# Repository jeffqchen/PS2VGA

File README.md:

# PS2VGA

This is an RGB+CSync video and stereo audio analogue output dongle, with a VGA port, a 3.5mm jack and an RCA jack, for the entire PlayStation family. It is a member from my [Console VGA Dongle Series](https://github.com/jeffqchen/Console-VGA-Dongle-Series).

Please refer to the **[Project Wiki](https://github.com/jeffqchen/PS2VGA/wiki)** regarding technical details, parts and building guide.

---------
## Special Thanks

- Mike Chi of [RetroTINK](https://www.retrotink.com) - [Twitter](https://twitter.com/retrotink2)

- Javier Rodas - [Twitter](https://twitter.com/JaviRodasG)

- Retro Gamer Stuff (Bad_Ad84) - [Twitter](https://twitter.com/RetroGamerStuff)

--------
Shield: [![CC BY-SA 4.0][cc-by-sa-shield]][cc-by-sa]

This work is licensed under a
[Creative Commons Attribution-ShareAlike 4.0 International License][cc-by-sa].

[![CC BY-SA 4.0][cc-by-sa-image]][cc-by-sa]

[cc-by-sa]: http://creativecommons.org/licenses/by-sa/4.0/
[cc-by-sa-image]: https://licensebuttons.net/l/by-sa/4.0/88x31.png
[cc-by-sa-shield]: https://img.shields.io/badge/License-CC%20BY--SA%204.0-lightgrey.svg

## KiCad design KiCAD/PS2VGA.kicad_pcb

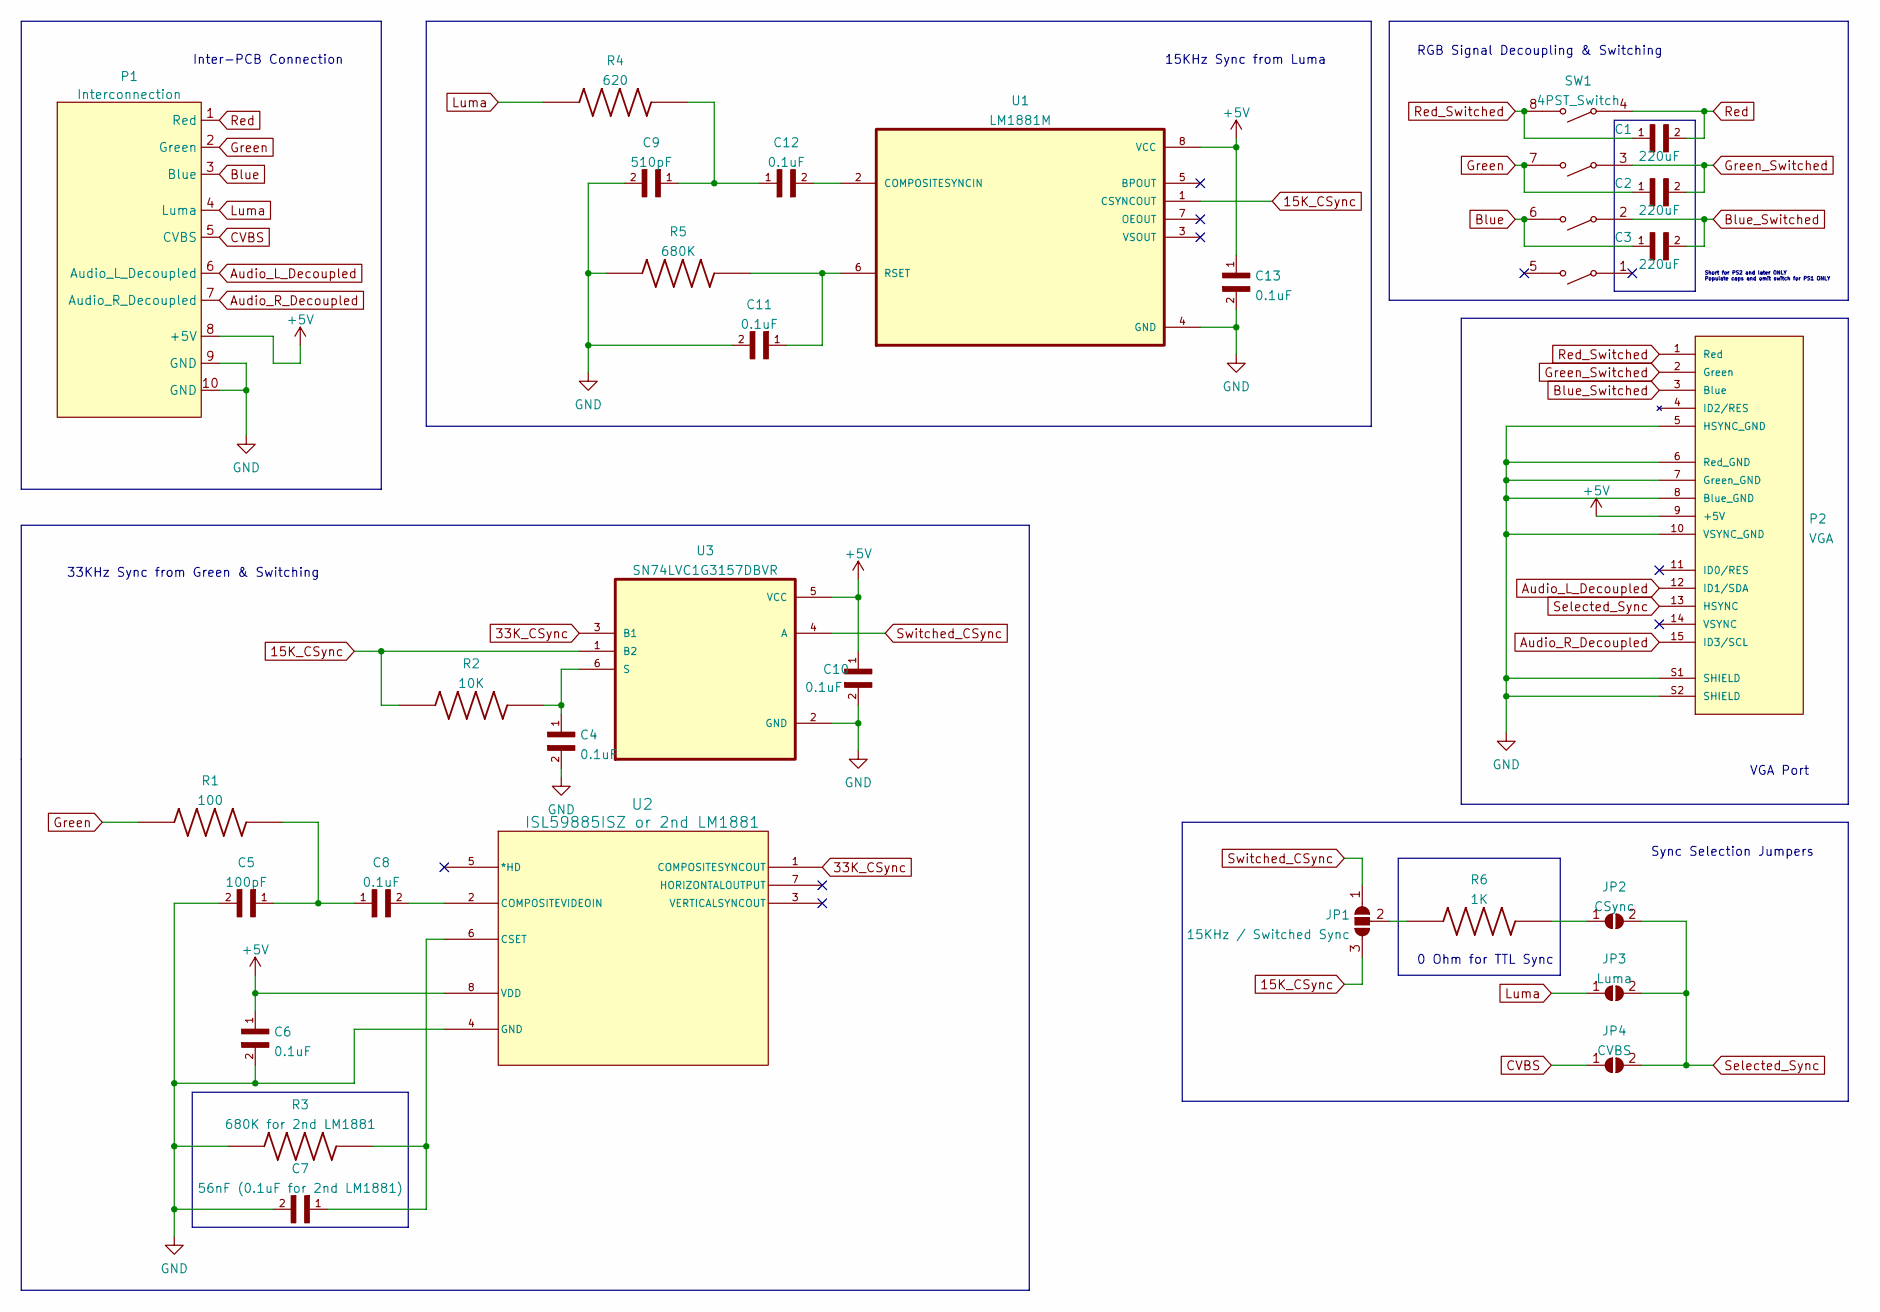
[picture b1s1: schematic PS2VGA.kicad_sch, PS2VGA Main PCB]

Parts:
C1, C2, C3: 220uF; C_1206_3216Metric
C4, C6, C8, C10, C11, C12, C13: 0.1uF; C_0603_1608Metric
C5: 100pF; C_0603_1608Metric
C7: 56nF (0.1uF for 2nd LM1881); C_0603_1608Metric
C9: 510pF; C_0603_1608Metric
JP1: 15KHz / Switched Sync; SolderJumper-3_P1.3mm_Open_RoundedPad1.0x1.5mm
JP2: CSync; SolderJumper-2_P1.3mm_Open_RoundedPad1.0x1.5mm
JP3: Luma; SolderJumper-2_P1.3mm_Open_RoundedPad1.0x1.5mm
JP4: CVBS; SolderJumper-2_P1.3mm_Open_RoundedPad1.0x1.5mm
P1: Interconnection
P2: VGA; VGA_female_rightangle_slim
R1: 100; R_0603_1608Metric
R2: 10K; R_0603_1608Metric
R3: 680K for 2nd LM1881; R_0603_1608Metric
R4: 620; R_0603_1608Metric
R5: 680K; R_0603_1608Metric
R6: 1K; R_0603_1608Metric
SW1: 4PST_Switch; 4PST Switch
U1: LM1881M; LM1881
U2: ISL59885ISZ or 2nd LM1881; ISL59885ISZ-ND
U3: SN74LVC1G3157DBVR

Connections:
15K_CSync: JP1.3 (B), R2.1, U1.1 (CSYNCOUT), U3.1 (B2); also elsewhere on the board
33K_CSync: U2.1 (COMPOSITESYNCOUT), U3.3 (B1)
+5V: C6.1, C10.1, C13.1, P1.8 (+5V), P2.9 (+5V), U1.8 (VCC), U2.8 (VDD), U3.5 (VCC); also elsewhere on the board
Audio_L_Decoupled: P1.6 (Audio_L_Decoupled), P2.12 (ID1/SDA)
Audio_R_Decoupled: P1.7 (Audio_R_Decoupled), P2.15 (ID3/SCL)
Blue: C3.1, P1.3 (Blue), SW1.6
Blue_Switched: C3.2, P2.3 (Blue), SW1.2
CVBS: JP4.1 (A), P1.5 (CVBS)
GND: C4.2, C5.2, C6.2, C7.2, C9.2, C10.2, C11.2, C13.2, P1.9 (GND), P1.10 (GND), P2.5 (HSYNC_GND), P2.6 (Red_GND), P2.7 (Green_GND), P2.8 (Blue_GND), P2.10 (VSYNC_GND), P2.S1 (SHIELD), P2.S2 (SHIELD), R3.1, R5.1, U1.4 (GND), U2.4 (GND), U3.2 (GND); also elsewhere on the board
Green: C2.1, P1.2 (Green), R1.1, SW1.7
Green_Switched: C2.2, P2.2 (Green), SW1.3
Luma: JP3.1 (A), P1.4 (Luma), R4.1
unnamed: C4.1, R2.2, U3.6 (S)
unnamed: C5.1, C8.1, R1.2
unnamed: C7.1, R3.2, U2.6 (CSET)
unnamed: C8.2, U2.2 (COMPOSITEVIDEOIN)
unnamed 16: C11.1, R5.2, U1.6 (RSET); also elsewhere on the board
unnamed: C9.1, C12.1, R4.2
unnamed 18: C12.2, U1.2 (COMPOSITESYNCIN); also elsewhere on the board
unnamed: JP1.2 (C), R6.1
unnamed: JP2.1 (A), R6.2
Red: C1.2, P1.1 (Red), SW1.4
Red_Switched: C1.1, P2.1 (Red), SW1.8
Selected_Sync: JP2.2 (B), JP3.2 (B), JP4.2 (B), P2.13 (HSYNC)
Switched_CSync: JP1.1 (A), U3.4 (A)

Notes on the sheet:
RGB Signal Decoupling & Switching
33KHz Sync from Green & Switching
0 Ohm for TTL Sync
Inter-PCB Connection
VGA Port
Short for PS2 and later ONLY Populate caps and omit switch for PS1 ONLY
15KHz Sync from Luma
Sync Selection Jumpers

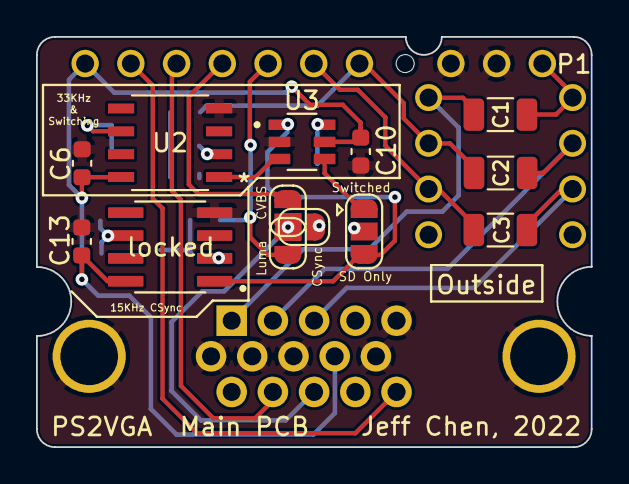
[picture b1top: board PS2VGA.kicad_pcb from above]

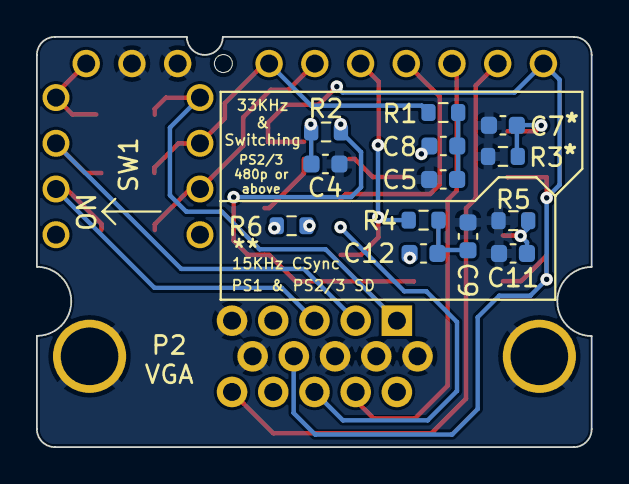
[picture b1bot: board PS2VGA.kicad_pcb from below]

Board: 2 copper layers, 30.8 x 22.8 mm, 29 parts (15 on the bottom side), 25 nets.

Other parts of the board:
locked: LM1881M; LM1881

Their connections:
15K_CSync: locked.1 (CSYNCOUT); also elsewhere on the board
+5V: locked.8 (VCC); also elsewhere on the board
GND: locked.4 (GND); also elsewhere on the board
unnamed 16: locked.6 (RSET); also elsewhere on the board
unnamed 18: locked.2 (COMPOSITESYNCIN); also elsewhere on the board

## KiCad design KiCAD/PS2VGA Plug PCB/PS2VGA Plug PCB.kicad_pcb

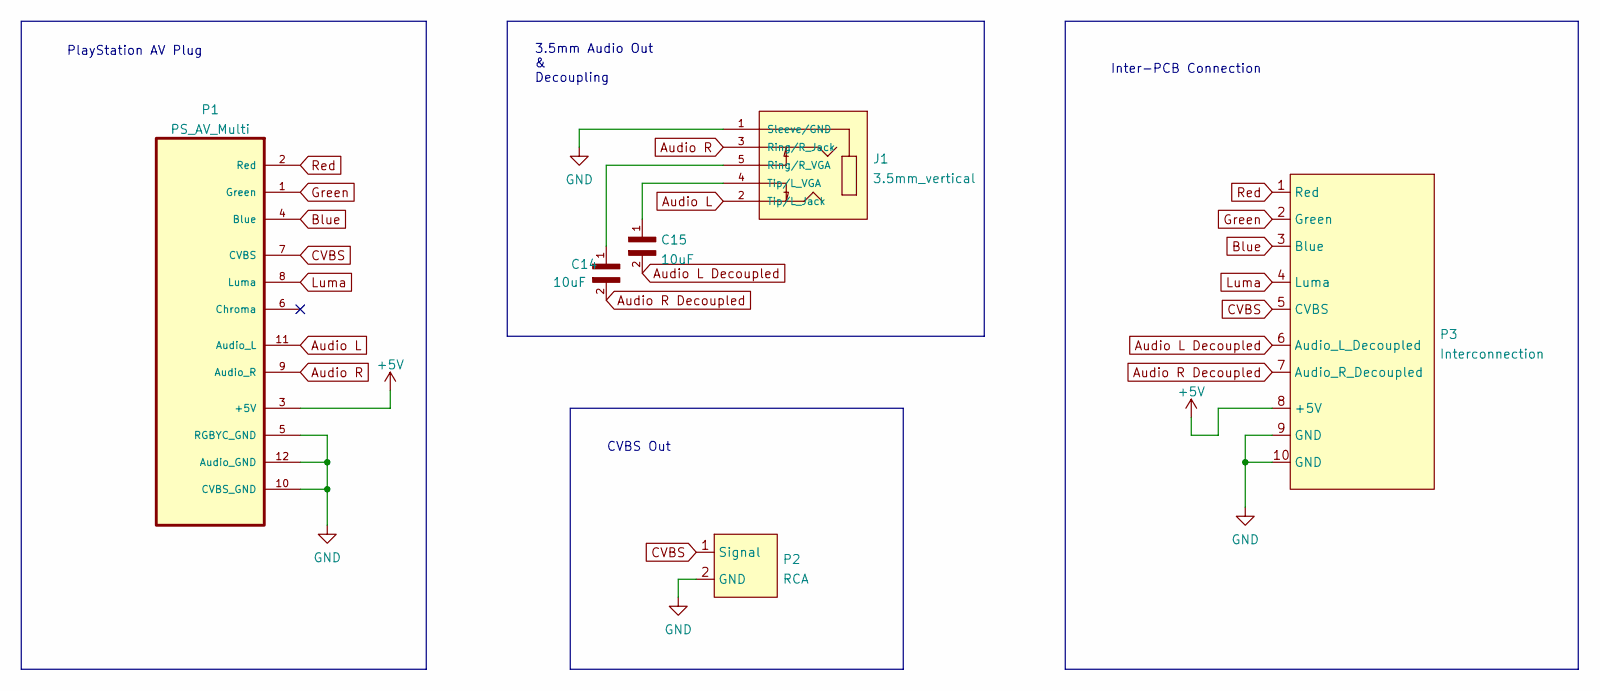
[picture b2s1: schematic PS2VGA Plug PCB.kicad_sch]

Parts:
C14, C15: 10uF; C_0603_1608Metric
J1: 3.5mm_vertical; PARTREV 1.01
P1: PS_AV_Multi
P2: RCA
P3: Interconnection

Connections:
+5V: P1.3 (+5V), P3.8 (+5V)
Audio L: J1.2 (Tip/L_Jack), P1.11 (Audio_L)
Audio L Decoupled: C15.2, P3.6 (Audio_L_Decoupled)
Audio R: J1.3 (Ring/R_Jack), P1.9 (Audio_R)
Audio R Decoupled: C14.2, P3.7 (Audio_R_Decoupled)
Blue: P1.4 (Blue), P3.3 (Blue)
CVBS: P1.7 (CVBS), P2.1 (Signal), P3.5 (CVBS)
GND: J1.1 (Sleeve/GND), P1.5 (RGBYC_GND), P1.10 (CVBS_GND), P1.12 (Audio_GND), P2.2 (GND), P3.9 (GND), P3.10 (GND)
Green: P1.1 (Green), P3.2 (Green)
Luma: P1.8 (Luma), P3.4 (Luma)
unnamed: C14.1, J1.5 (Ring/R_VGA)
unnamed: C15.1, J1.4 (Tip/L_VGA)
Red: P1.2 (Red), P3.1 (Red)

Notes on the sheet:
CVBS Out
Inter-PCB Connection
PlayStation AV Plug
3.5mm Audio Out & Decoupling

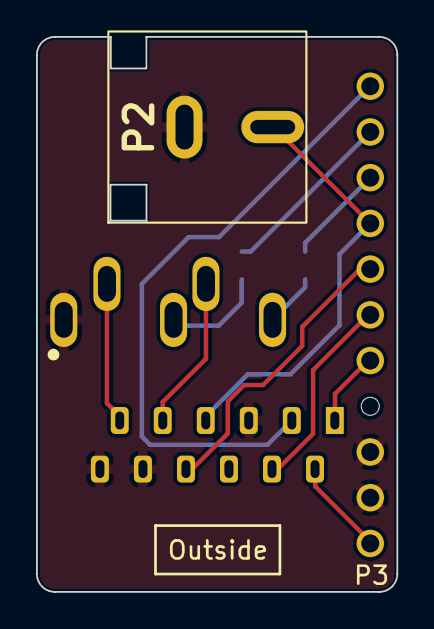
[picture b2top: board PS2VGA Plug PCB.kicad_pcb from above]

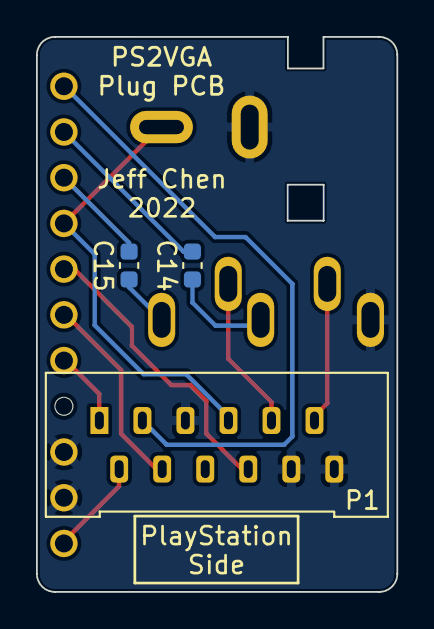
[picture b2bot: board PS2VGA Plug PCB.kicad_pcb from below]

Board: 2 copper layers, 20.0 x 30.8 mm, 6 parts (3 on the bottom side), 13 nets.

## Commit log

2022-07-11 Upload Pics
2022-07-11 3D Print Models
2022-07-11 More photos for guide
2022-07-11 KiCAD files
2022-07-11 Add PCB shot
2022-07-14 Rename pic
2022-07-14 Add HA install pics
2022-08-09 Add license

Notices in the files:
parts and their libraries:
Copyright 2021 Accelerated Designs. All rights reserved.
